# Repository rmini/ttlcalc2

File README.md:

# TtlCalc2 Project

## Overview

The TtlCalc2 project is a recreation of the original (now TtlCalc1) project from 2005 that implemented a four-function floating point calculator in TTL logic without a microprocessor.

This version uses multilayer PCBs and Nixie tube and neon indicators for the display, whereas the original used wire wrap boards and LED 7-segment displays. Both versions share the same architecture, with separate (Harvard architecture) 8-bit data and 12-bit instruction address spaces, a 4-bit data path, and a 16-bit instruction word.

The goal of the original was to gain experience designing and implementing a processor with these techniques with an eye towards taking on the design of a more capable minicomputer. 

This repository contains the hardware and software components for the TtlCalc2 project, including simulation tools, assembly code, and documentation.

## Board renders

### Main logic board (processor)

### Display driver board

### Front panel display board (Nixies and neons)

## Directory Structure

 * [`hw/`](hw/): KiCad schematic and PCB designs for the hardware
 * [`sw/`](sw/): Software for the calculator (microinstruction ROMs)
 * [`doc/`](doc/): Design and implementation documentation
 * [`TtlCalcSim/`](TtlCalcSim/): Simulator for the calculator hardware

## Hardware

The [`hw`](hw) directory contains KiCad project files for the TtlCalc2 hardware design.

- [`ttlcalc2/`](hw/ttlcalc2/): Logic board hardware design files.
- [`ttlcalc2_display/`](hw/ttlcalc2_display/): Display driver module design files.
- [`ttlcalc2_front/`](hw/ttlcalc2_front/): Front panel design files.

TODO: The keyboard and keyboard interface still needs to be designed.

### Gerber Files

The `hw/ttlcalc2/gerbers` directory contains the Gerber files for PCB manufacturing.

## Software

The [`sw`](sw/) directory contains assembly code for the TtlCalc2 project. This project uses the [customasm](https://github.com/hlorenzi/customasm) assembler (v0.14.0 or later) to generate the microcode stream.

- [`ttlcalc2.asm`](sw/ttlcalc2.asm): Mnemonic definitions for the TtlCalc2 microcode.
- [`fib.asm`](sw/fib.asm): Assembly code for calculating Fibonacci numbers.

TODO: Port original ttlcalc assembly source code to new customasm syntax.

### Assembling

For example, to build the Fibonacci code, run:
```sh
customasm fib.asm
```
This generates `fib.bin` which you can then load into the simulator and run.

## Documentation

The [`doc`](doc/) directory contains documentation for the TtlCalc2 project.

## Simulation

The [`TtlCalcSim`](TtlCalcSim/) directory contains the simulation tools for the TtlCalc2 project. The simulator is implemented as a C#/.NET 9.0 console application.

- [`TtlCalcSim/`](TtlCalcSim/TtlCalcSim/): Core simulation library.
- [`TtlCalcSim.ConsoleUI/`](TtlCalcSim/TtlCalcSim.ConsoleUI/): Console-based user interface for the simulator.
- [`TtlCalcSim.Tests/`](TtlCalcSim/TtlCalcSim.Tests/): Unit tests for the simulation library.
- [`TtlCalcSim.Testing/`](TtlCalcSim/TtlCalcSim.Testing/): Helpers for testing assembly programs in the simulator.
- [`TtlCalcSim.ProgramTests/`](TtlCalcSim/TtlCalcSim.ProgramTests/): Tests that assemble programs from [`sw`](sw/) and run them in the simulator, including end-to-end checks of each instruction against the documented behavior.

### Building the Simulator

To build the simulator, open the TtlCalcSim.sln solution file in Visual Studio and build the project, or use the following command from the TtlCalcSim directory:
```sh
dotnet build
```

### Running Tests

To run the unit tests, use the following command from the TtlCalcSim directory:
```sh
dotnet test
```

The program tests assemble source at test time, so they need customasm v0.14.0 or later on `PATH`, or the `CUSTOMASM` environment variable set to its location.

### Testing programs

`TtlCalcSim.Testing` assembles a program with customasm and loads it into a `TestMachine`, which can set up state, run to labels, and inspect results by symbol name:
```csharp
var m = new TestMachine(AsmProgram.AssembleSw("fib.asm"));
m.RunUntil("numloop");                         // program labels; fails if the step limit is hit
Assert.Equal(0x1, m.Mem["src1h"]);             // memory by address or data label
m.RunToEnd(maxSteps: 10_000);
Assert.Equal(832040, m.ReadNumber(0xF8, 8));   // BCD, least significant digit first
```

`StartAt("label")` begins execution elsewhere, so a loop body can be tested in isolation after setting up memory and registers.

`AsmProgram.FromSource` assembles a snippet with the TtlCalc2 rules included, which is useful for testing individual instructions. I/O writes are recorded in `IoWrites`, and input is supplied with `QueueInput` or `OnInput`; reading an address with no input fails the test.

### Running the simulator

Either run the simulator executable after building, or run it via the `dotnet` command:
```sh
dotnet run --project TtlCalcSim.ConsoleUI
```

## License

This project is licensed under the MIT License. See the LICENSE file for details.

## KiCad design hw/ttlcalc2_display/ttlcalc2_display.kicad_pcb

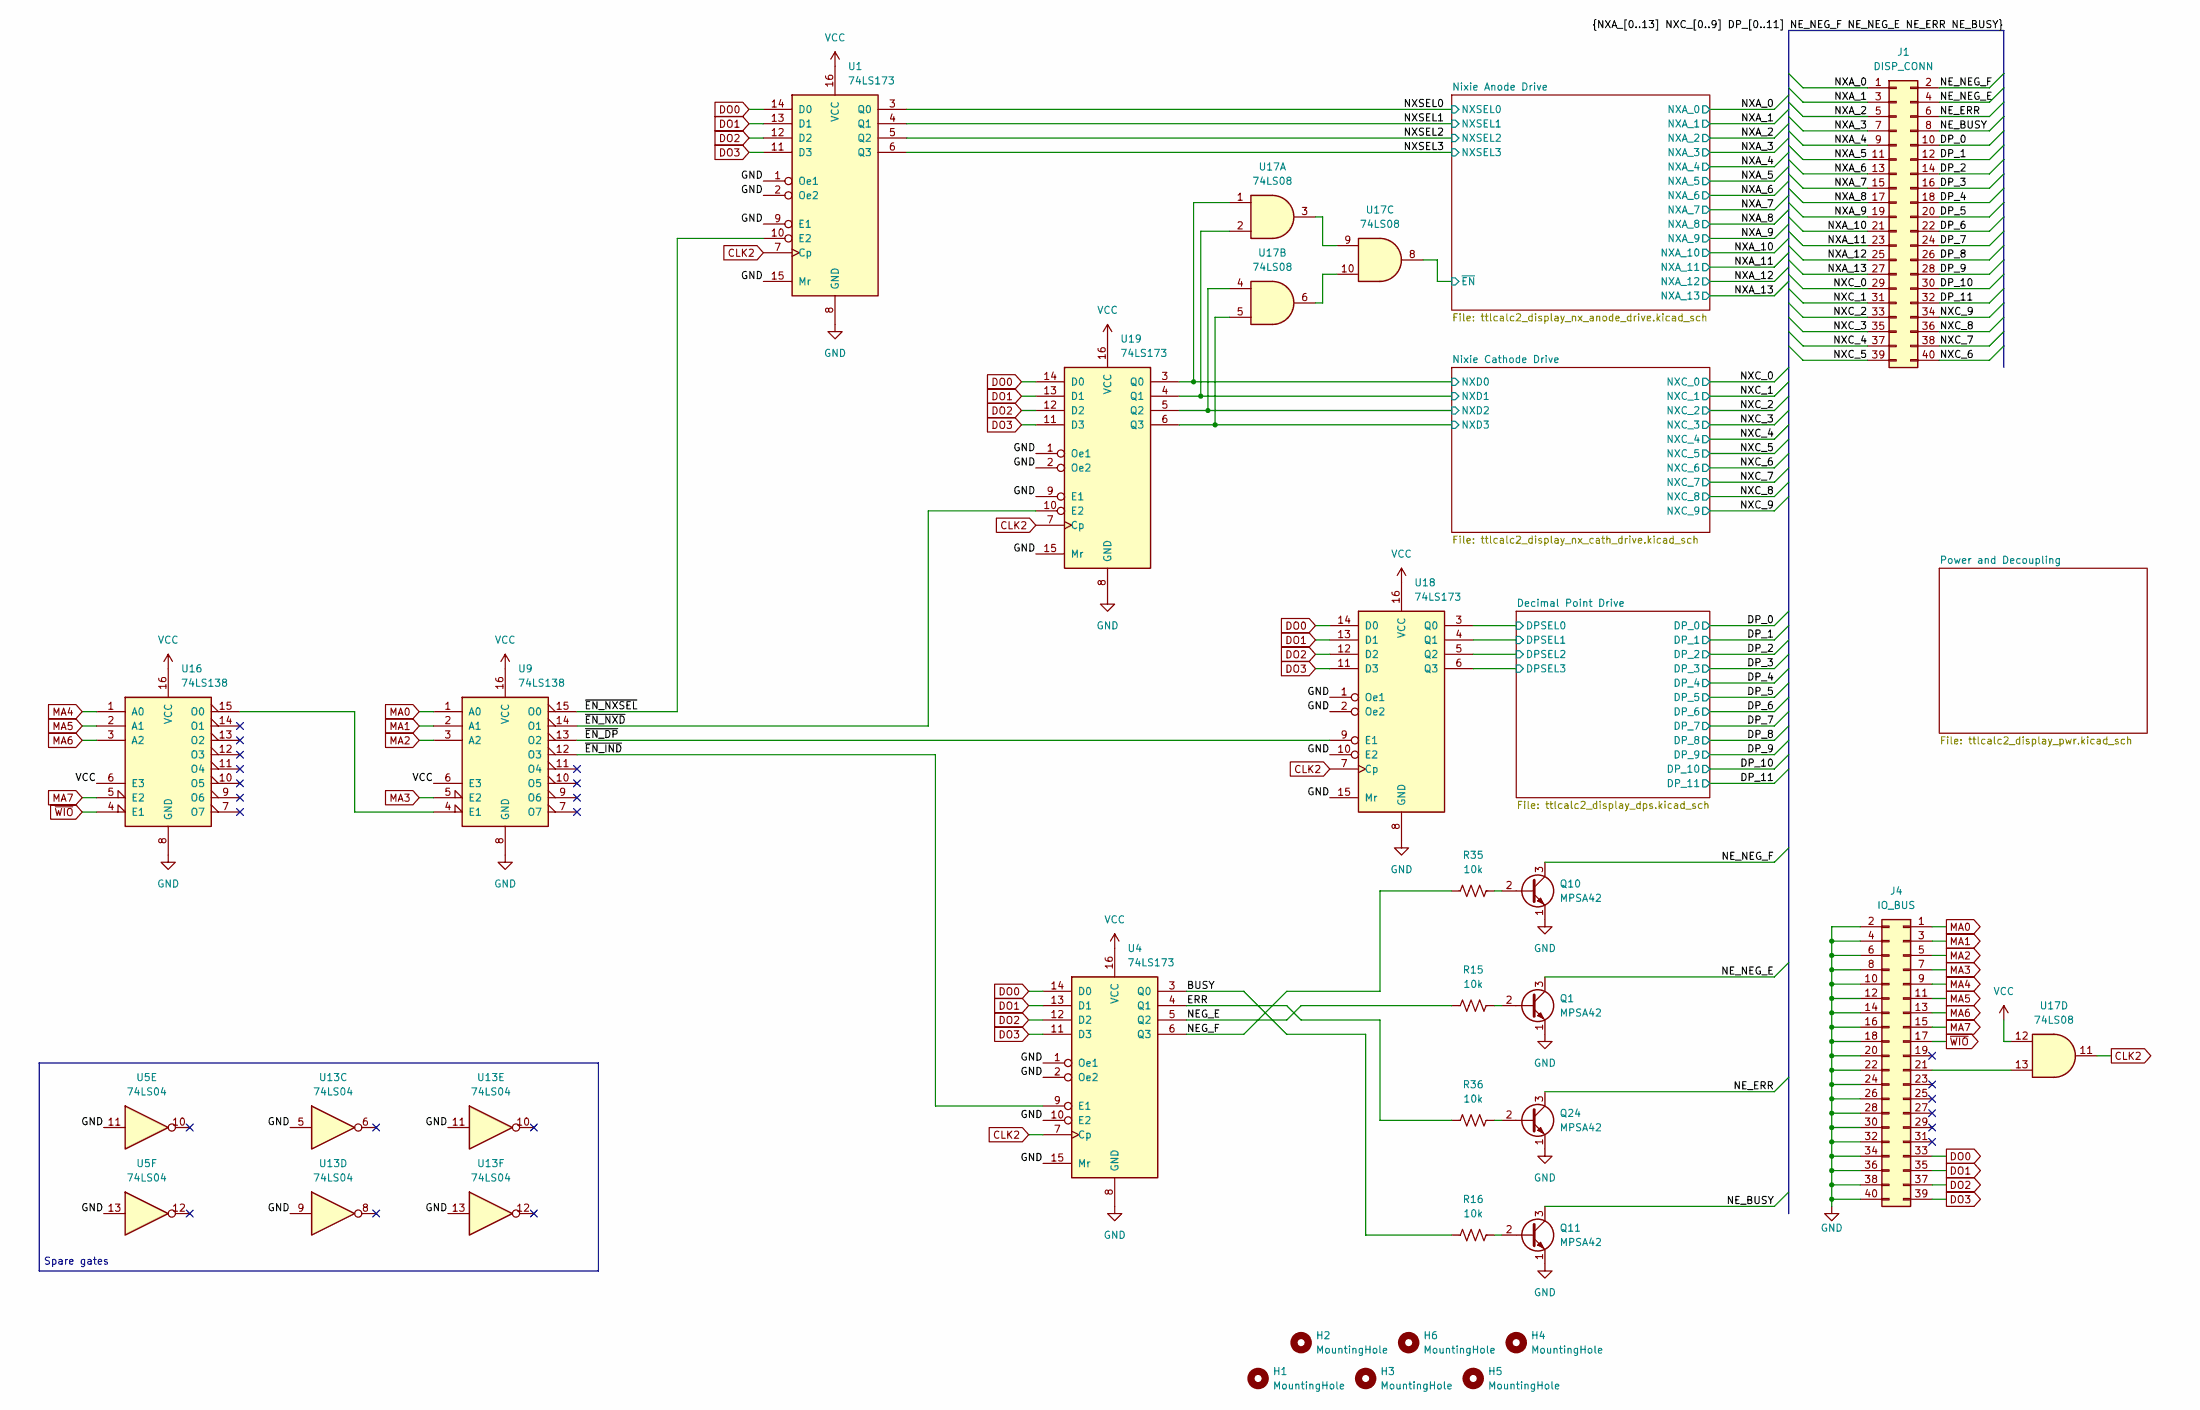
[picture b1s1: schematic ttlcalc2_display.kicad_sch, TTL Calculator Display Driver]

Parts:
H1, H2, H3, H4, H5, H6: MountingHole; MountingHole_3.2mm_M3
J1: DISP_CONN; IDC-Header_2x20_P2.54mm_Vertical
J4: IO_BUS; PinHeader_2x20_P2.54mm_Vertical
Q1, Q10, Q11, Q24: MPSA42; TO-92_Inline_Wide
R15, R16, R35, R36: 10k; R_Axial_DIN0207_L6.3mm_D2.5mm_P7.62mm_Horizontal
U1, U4, U18, U19: 74LS173; DIP-16_W7.62mm
U5, U13: 74LS04; DIP-14_W7.62mm
U9, U16: 74LS138; DIP-16_W7.62mm
U17: 74LS08; DIP-14_W7.62mm

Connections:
/BUSY: R16.1, U4.3 (Q0)
/DP_0: J1.10; also elsewhere on the board
/DP_1: J1.12; also elsewhere on the board
/DP_2: J1.14; also elsewhere on the board
/DP_3: J1.16; also elsewhere on the board
/DP_4: J1.18; also elsewhere on the board
/DP_5: J1.20; also elsewhere on the board
/DP_6: J1.22; also elsewhere on the board
/DP_7: J1.24; also elsewhere on the board
/DP_8: J1.26; also elsewhere on the board
/DP_9: J1.28; also elsewhere on the board
/DP_10: J1.30; also elsewhere on the board
/DP_11: J1.32; also elsewhere on the board
/Decimal Point Drive/DPSEL0: U18.3 (Q0); also elsewhere on the board
/Decimal Point Drive/DPSEL1: U18.4 (Q1); also elsewhere on the board
/Decimal Point Drive/DPSEL2: U18.5 (Q2); also elsewhere on the board
/Decimal Point Drive/DPSEL3: U18.6 (Q3); also elsewhere on the board
/ERR: R36.1, U4.4 (Q1)
/NEG_E: R15.1, U4.5 (Q2)
/NEG_F: R35.1, U4.6 (Q3)
/NE_BUSY: J1.8, Q11.3 (C)
/NE_ERR: J1.6, Q24.3 (C)
/NE_NEG_E: J1.4, Q1.3 (C)
/NE_NEG_F: J1.2, Q10.3 (C)
/NXA_0: J1.1; also elsewhere on the board
/NXA_1: J1.3; also elsewhere on the board
/NXA_2: J1.5; also elsewhere on the board
/NXA_3: J1.7; also elsewhere on the board
/NXA_4: J1.9; also elsewhere on the board
/NXA_5: J1.11; also elsewhere on the board
/NXA_6: J1.13; also elsewhere on the board
/NXA_7: J1.15; also elsewhere on the board
/NXA_8: J1.17; also elsewhere on the board
/NXA_9: J1.19; also elsewhere on the board
/NXA_10: J1.21; also elsewhere on the board
/NXA_11: J1.23; also elsewhere on the board
/NXA_12: J1.25; also elsewhere on the board
/NXA_13: J1.27; also elsewhere on the board
/NXC_0: J1.29; also elsewhere on the board
/NXC_1: J1.31; also elsewhere on the board
/NXC_2: J1.33; also elsewhere on the board
/NXC_3: J1.35; also elsewhere on the board
/NXC_4: J1.37; also elsewhere on the board
/NXC_5: J1.39; also elsewhere on the board
/NXC_6: J1.40; also elsewhere on the board
/NXC_7: J1.38; also elsewhere on the board
/NXC_8: J1.36; also elsewhere on the board
/NXC_9: J1.34; also elsewhere on the board
/NXSEL0: U1.3 (Q0); also elsewhere on the board
/NXSEL1: U1.4 (Q1); also elsewhere on the board
/NXSEL2: U1.5 (Q2); also elsewhere on the board
/NXSEL3: U1.6 (Q3); also elsewhere on the board
/Nixie Anode Drive/~EN: U17.8; also elsewhere on the board
/Nixie Cathode Drive/NXD0: U17.1, U19.3 (Q0); also elsewhere on the board
/Nixie Cathode Drive/NXD1: U17.2, U19.4 (Q1); also elsewhere on the board
/Nixie Cathode Drive/NXD2: U17.4, U19.5 (Q2); also elsewhere on the board
/Nixie Cathode Drive/NXD3: U17.5, U19.6 (Q3); also elsewhere on the board
/~EN_DP: U9.13 (O2), U18.9 (E1)
/~EN_IND: U4.9 (E1), U9.12 (O3)
/~EN_NXD: U9.14 (O1), U19.10 (E2)
/~EN_NXSEL: U1.10 (E2), U9.15 (O0)
CLK2: U1.7 (Cp), U4.7 (Cp), U17.11, U18.7 (Cp), U19.7 (Cp)
DO0: J4.33, U1.14 (D0), U4.14 (D0), U18.14 (D0), U19.14 (D0)
DO1: J4.35, U1.13 (D1), U4.13 (D1), U18.13 (D1), U19.13 (D1)
DO2: J4.37, U1.12 (D2), U4.12 (D2), U18.12 (D2), U19.12 (D2)
DO3: J4.39, U1.11 (D3), U4.11 (D3), U18.11 (D3), U19.11 (D3)
GND: J4.2, J4.4, J4.6, J4.8, J4.10, J4.12, J4.14, J4.16, J4.18, J4.20, J4.22, J4.24, J4.26, J4.28, J4.30, J4.32, J4.34, J4.36, J4.38, J4.40, Q1.1 (E), Q10.1 (E), Q11.1 (E), Q24.1 (E), U1.1 (Oe1), U1.2 (Oe2), U1.8 (GND), U1.9 (E1), U1.15 (Mr), U4.1 (Oe1), U4.2 (Oe2), U4.8 (GND), U4.10 (E2), U4.15 (Mr), U5.11, U5.13, U9.8 (GND), U13.5, U13.9, U13.11, U13.13, U16.8 (GND), U18.1 (Oe1), U18.2 (Oe2), U18.8 (GND), U18.10 (E2), U18.15 (Mr), U19.1 (Oe1), U19.2 (Oe2), U19.8 (GND), U19.9 (E1), U19.15 (Mr); also elsewhere on the board
MA0: J4.1, U9.1 (A0)
MA1: J4.3, U9.2 (A1)
MA2: J4.5, U9.3 (A2)
MA3: J4.7, U9.5 (E2)
MA4: J4.9, U16.1 (A0)
MA5: J4.11, U16.2 (A1)
MA6: J4.13, U16.3 (A2)
MA7: J4.15, U16.5 (E2)
unnamed: J4.21, U17.13
unnamed: Q1.2 (B), R15.2
unnamed: Q10.2 (B), R35.2
unnamed: Q11.2 (B), R16.2
unnamed: Q24.2 (B), R36.2
unnamed: U9.4 (E1), U16.15 (O0)
unnamed: U17.3, U17.9
unnamed: U17.6, U17.10
VCC: U1.16 (VCC), U4.16 (VCC), U9.6 (E3), U9.16 (VCC), U16.6 (E3), U16.16 (VCC), U17.12, U18.16 (VCC), U19.16 (VCC); also elsewhere on the board
~WIO: J4.17, U16.4 (E1)

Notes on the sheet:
Spare gates

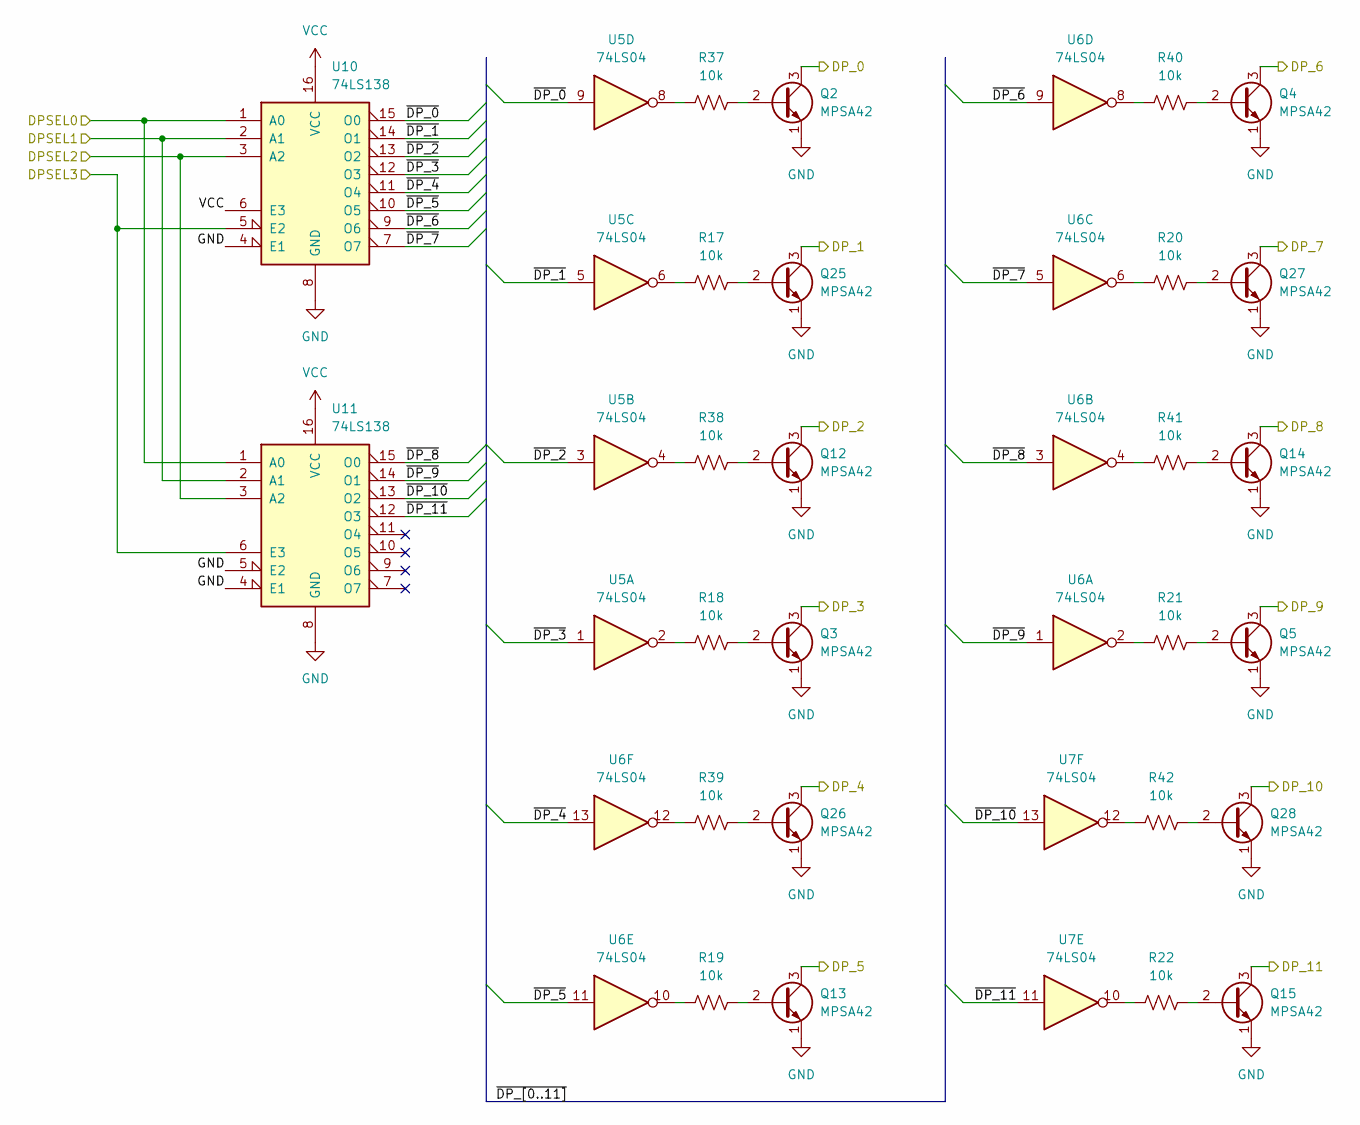
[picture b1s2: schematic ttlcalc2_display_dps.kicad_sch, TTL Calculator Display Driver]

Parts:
Q2, Q3, Q4, Q5, Q12, Q13, Q14, Q15, Q25, Q26, Q27, Q28: MPSA42; TO-92_Inline_Wide
R17, R18, R19, R20, R21, R22, R37, R38, R39, R40, R41, R42: 10k; R_Axial_DIN0207_L6.3mm_D2.5mm_P7.62mm_Horizontal
U5, U6, U7: 74LS04; DIP-14_W7.62mm
U10, U11: 74LS138; DIP-16_W7.62mm

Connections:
/DP_0: Q2.3 (C); also elsewhere on the board
/DP_1: Q25.3 (C); also elsewhere on the board
/DP_2: Q12.3 (C); also elsewhere on the board
/DP_3: Q3.3 (C); also elsewhere on the board
/DP_4: Q26.3 (C); also elsewhere on the board
/DP_5: Q13.3 (C); also elsewhere on the board
/DP_6: Q4.3 (C); also elsewhere on the board
/DP_7: Q27.3 (C); also elsewhere on the board
/DP_8: Q14.3 (C); also elsewhere on the board
/DP_9: Q5.3 (C); also elsewhere on the board
/DP_10: Q28.3 (C); also elsewhere on the board
/DP_11: Q15.3 (C); also elsewhere on the board
/Decimal Point Drive/DPSEL0: U10.1 (A0), U11.1 (A0); also elsewhere on the board
/Decimal Point Drive/DPSEL1: U10.2 (A1), U11.2 (A1); also elsewhere on the board
/Decimal Point Drive/DPSEL2: U10.3 (A2), U11.3 (A2); also elsewhere on the board
/Decimal Point Drive/DPSEL3: U10.5 (E2), U11.6 (E3); also elsewhere on the board
/Decimal Point Drive/~DP_0: U5.9, U10.15 (O0)
/Decimal Point Drive/~DP_1: U5.5, U10.14 (O1)
/Decimal Point Drive/~DP_2: U5.3, U10.13 (O2)
/Decimal Point Drive/~DP_3: U5.1, U10.12 (O3)
/Decimal Point Drive/~DP_4: U6.13, U10.11 (O4)
/Decimal Point Drive/~DP_5: U6.11, U10.10 (O5)
/Decimal Point Drive/~DP_6: U6.9, U10.9 (O6)
/Decimal Point Drive/~DP_7: U6.5, U10.7 (O7)
/Decimal Point Drive/~DP_8: U6.3, U11.15 (O0)
/Decimal Point Drive/~DP_9: U6.1, U11.14 (O1)
/Decimal Point Drive/~DP_10: U7.13, U11.13 (O2)
/Decimal Point Drive/~DP_11: U7.11, U11.12 (O3)
GND: Q2.1 (E), Q3.1 (E), Q4.1 (E), Q5.1 (E), Q12.1 (E), Q13.1 (E), Q14.1 (E), Q15.1 (E), Q25.1 (E), Q26.1 (E), Q27.1 (E), Q28.1 (E), U10.4 (E1), U10.8 (GND), U11.4 (E1), U11.5 (E2), U11.8 (GND); also elsewhere on the board
unnamed: Q2.2 (B), R37.2
unnamed: Q3.2 (B), R18.2
unnamed: Q4.2 (B), R40.2
unnamed: Q5.2 (B), R21.2
unnamed: Q12.2 (B), R38.2
unnamed: Q13.2 (B), R19.2
unnamed: Q14.2 (B), R41.2
unnamed: Q15.2 (B), R22.2
unnamed: Q25.2 (B), R17.2
unnamed: Q26.2 (B), R39.2
unnamed: Q27.2 (B), R20.2
unnamed: Q28.2 (B), R42.2
unnamed: R17.1, U5.6
unnamed: R18.1, U5.2
unnamed: R19.1, U6.10
unnamed: R20.1, U6.6
unnamed: R21.1, U6.2
unnamed: R22.1, U7.10
unnamed: R37.1, U5.8
unnamed: R38.1, U5.4
unnamed: R39.1, U6.12
unnamed: R40.1, U6.8
unnamed: R41.1, U6.4
unnamed: R42.1, U7.12
VCC: U10.6 (E3), U10.16 (VCC), U11.16 (VCC); also elsewhere on the board

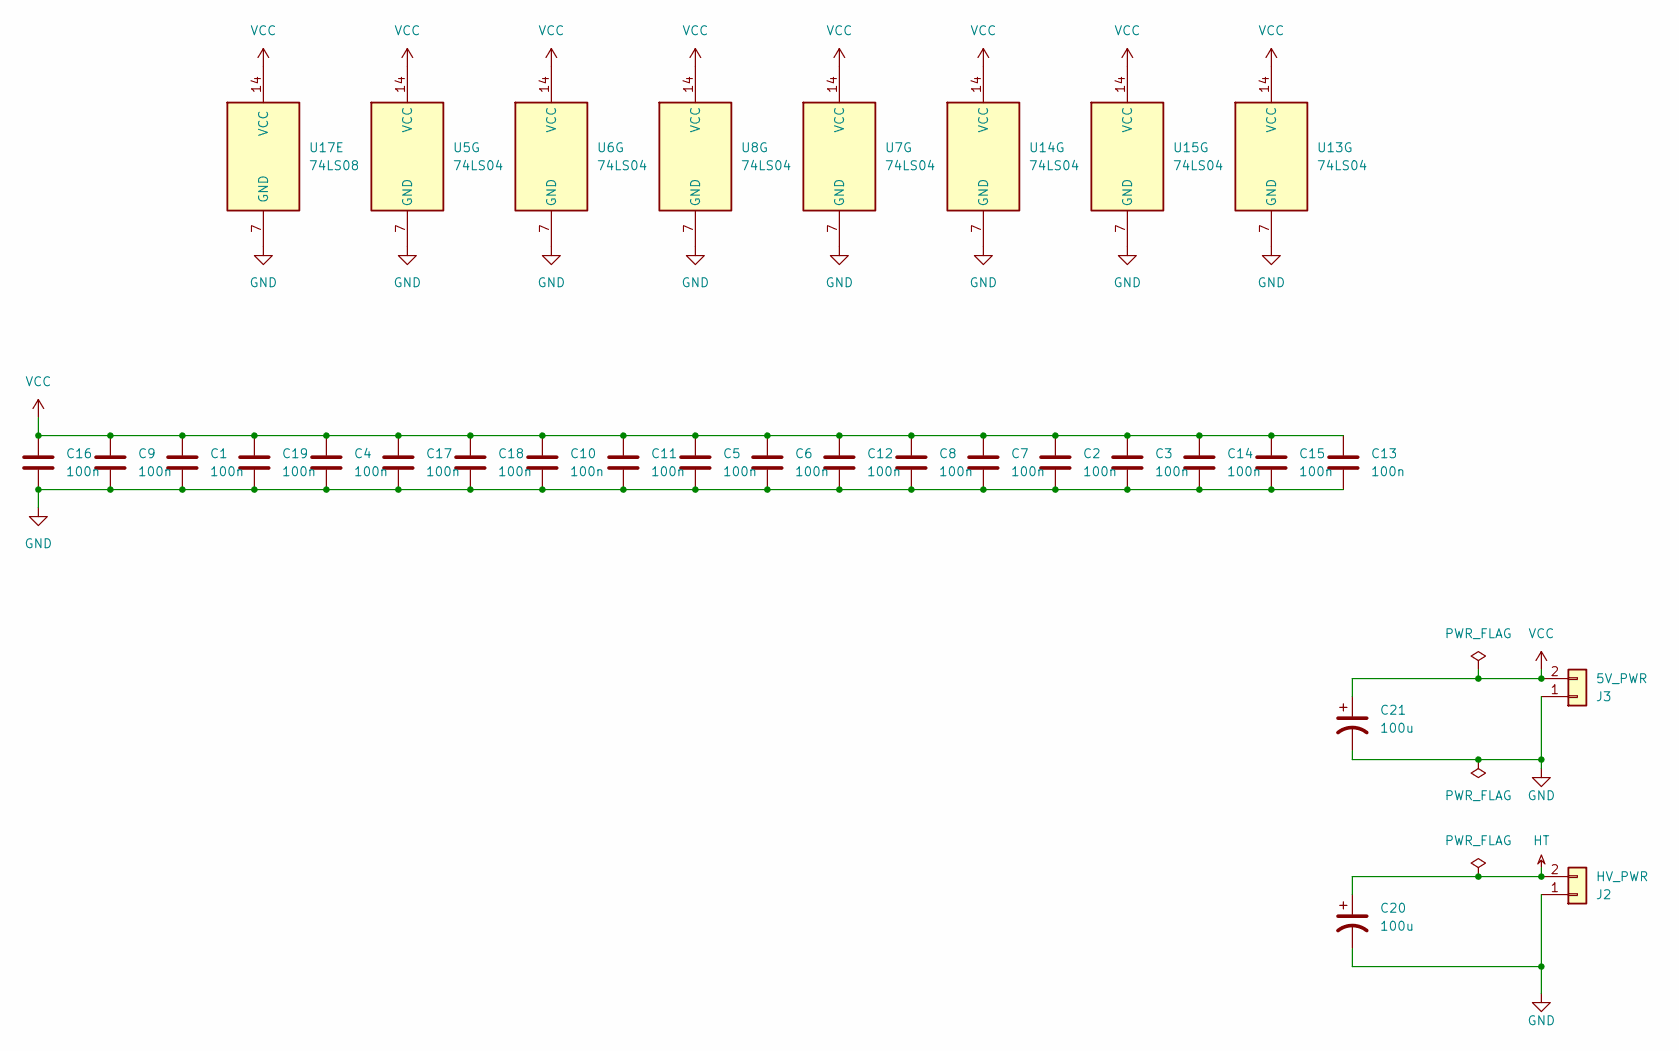
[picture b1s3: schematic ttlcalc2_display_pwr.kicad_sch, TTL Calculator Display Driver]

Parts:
C1, C2, C3, C4, C5, C6, C7, C8, C9, C10, C11, C12, C13, C14, C15, C16, C17, C18, C19: 100n; C_Axial_L3.8mm_D2.6mm_P7.50mm_Horizontal
C20: 100u; CP_Radial_D18.0mm_P7.50mm
C21: 100u; CP_Radial_D6.3mm_P2.50mm
J2: HV_PWR; TerminalBlock_Phoenix_MKDS-1,5-2-5.08_1x02_P5.08mm_Horizont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
J3: 5V_PWR; TerminalBlock_Phoenix_MKDS-1,5-2-5.08_1x02_P5.08mm_Horizont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
U5, U6, U7, U8, U13, U14, U15: 74LS04; DIP-14_W7.62mm
U17: 74LS08; DIP-14_W7.62mm

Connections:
GND: C1.2, C2.2, C3.2, C4.2, C5.2, C6.2, C7.2, C8.2, C9.2, C10.2, C11.2, C12.2, C13.2, C14.2, C15.2, C16.2, C17.2, C18.2, C19.2, C20.2, C21.2, J2.1, J3.1, U5.7 (GND), U6.7 (GND), U7.7 (GND), U8.7 (GND), U13.7 (GND), U14.7 (GND), U15.7 (GND), U17.7 (GND); also elsewhere on the board
HT: C20.1, J2.2; also elsewhere on the board
VCC: C1.1, C2.1, C3.1, C4.1, C5.1, C6.1, C7.1, C8.1, C9.1, C10.1, C11.1, C12.1, C13.1, C14.1, C15.1, C16.1, C17.1, C18.1, C19.1, C21.1, J3.2, U5.14 (VCC), U6.14 (VCC), U7.14 (VCC), U8.14 (VCC), U13.14 (VCC), U14.14 (VCC), U15.14 (VCC), U17.14 (VCC); also elsewhere on the board

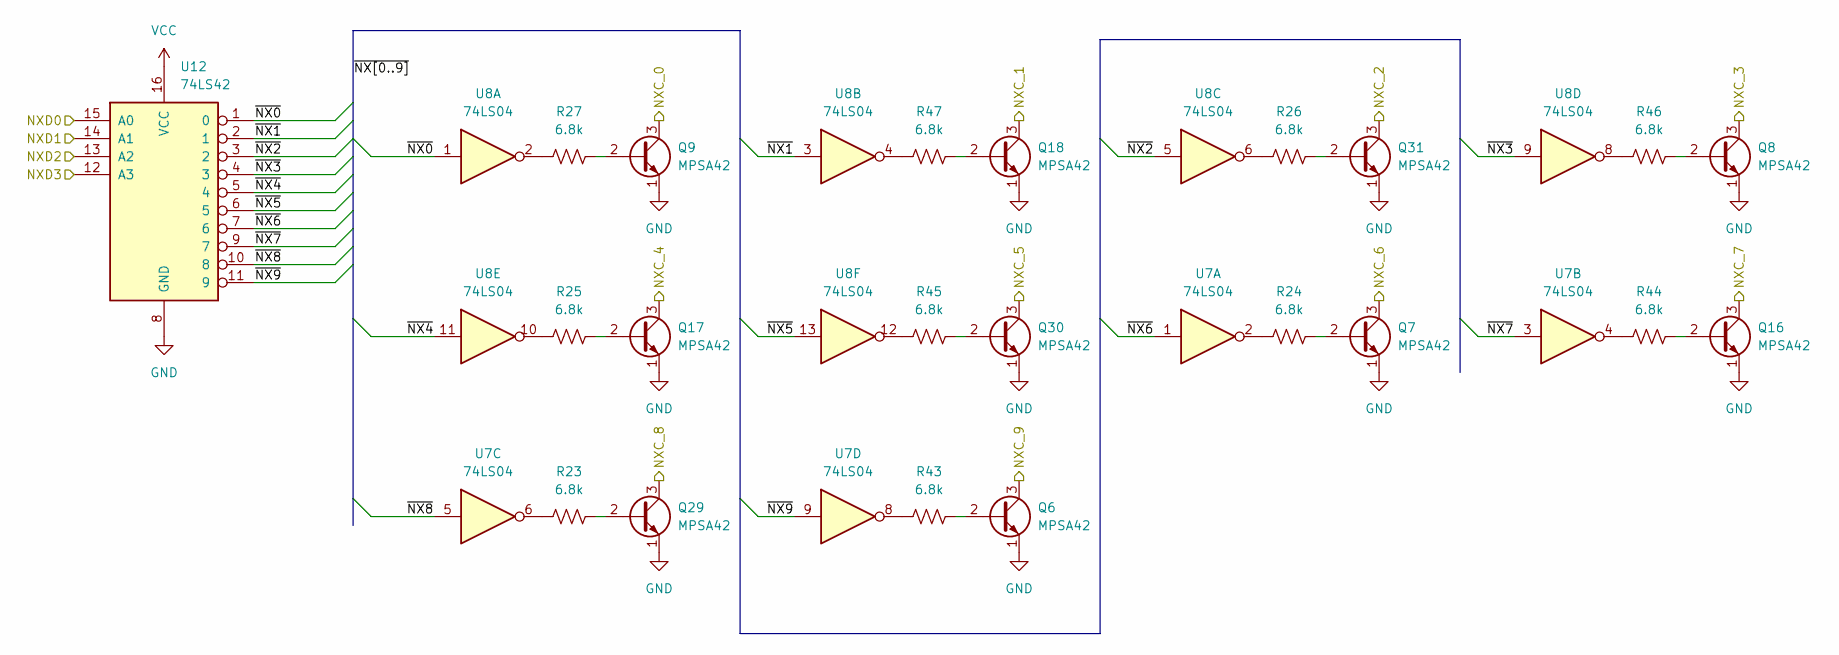
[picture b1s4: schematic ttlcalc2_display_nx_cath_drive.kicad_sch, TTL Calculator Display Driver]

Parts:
Q6, Q7, Q8, Q9, Q16, Q17, Q18, Q29, Q30, Q31: MPSA42; TO-92_Inline_Wide
R23, R24, R25, R26, R27, R43, R44, R45, R46, R47: 6.8k; R_Axial_DIN0207_L6.3mm_D2.5mm_P7.62mm_Horizontal
U7, U8: 74LS04; DIP-14_W7.62mm
U12: 74LS42; DIP-16_W7.62mm

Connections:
/NXC_0: Q9.3 (C); also elsewhere on the board
/NXC_1: Q18.3 (C); also elsewhere on the board
/NXC_2: Q31.3 (C); also elsewhere on the board
/NXC_3: Q8.3 (C); also elsewhere on the board
/NXC_4: Q17.3 (C); also elsewhere on the board
/NXC_5: Q30.3 (C); also elsewhere on the board
/NXC_6: Q7.3 (C); also elsewhere on the board
/NXC_7: Q16.3 (C); also elsewhere on the board
/NXC_8: Q29.3 (C); also elsewhere on the board
/NXC_9: Q6.3 (C); also elsewhere on the board
/Nixie Cathode Drive/NXD0: U12.15 (A0); also elsewhere on the board
/Nixie Cathode Drive/NXD1: U12.14 (A1); also elsewhere on the board
/Nixie Cathode Drive/NXD2: U12.13 (A2); also elsewhere on the board
/Nixie Cathode Drive/NXD3: U12.12 (A3); also elsewhere on the board
/Nixie Cathode Drive/~NX0: U8.1, U12.1 (0)
/Nixie Cathode Drive/~NX1: U8.3, U12.2 (1)
/Nixie Cathode Drive/~NX2: U8.5, U12.3 (2)
/Nixie Cathode Drive/~NX3: U8.9, U12.4 (3)
/Nixie Cathode Drive/~NX4: U8.11, U12.5 (4)
/Nixie Cathode Drive/~NX5: U8.13, U12.6 (5)
/Nixie Cathode Drive/~NX6: U7.1, U12.7 (6)
/Nixie Cathode Drive/~NX7: U7.3, U12.9 (7)
/Nixie Cathode Drive/~NX8: U7.5, U12.10 (8)
/Nixie Cathode Drive/~NX9: U7.9, U12.11 (9)
GND: Q6.1 (E), Q7.1 (E), Q8.1 (E), Q9.1 (E), Q16.1 (E), Q17.1 (E), Q18.1 (E), Q29.1 (E), Q30.1 (E), Q31.1 (E), U12.8 (GND); also elsewhere on the board
unnamed: Q6.2 (B), R43.2
unnamed: Q7.2 (B), R24.2
unnamed: Q8.2 (B), R46.2
unnamed: Q9.2 (B), R27.2
unnamed: Q16.2 (B), R44.2
unnamed: Q17.2 (B), R25.2
unnamed: Q18.2 (B), R47.2
unnamed: Q29.2 (B), R23.2
unnamed: Q30.2 (B), R45.2
unnamed: Q31.2 (B), R26.2
unnamed: R23.1, U7.6
unnamed: R24.1, U7.2
unnamed: R25.1, U8.10
unnamed: R26.1, U8.6
unnamed: R27.1, U8.2
unnamed: R43.1, U7.8
unnamed: R44.1, U7.4
unnamed: R45.1, U8.12
unnamed: R46.1, U8.8
unnamed: R47.1, U8.4
VCC: U12.16 (VCC); also elsewhere on the board

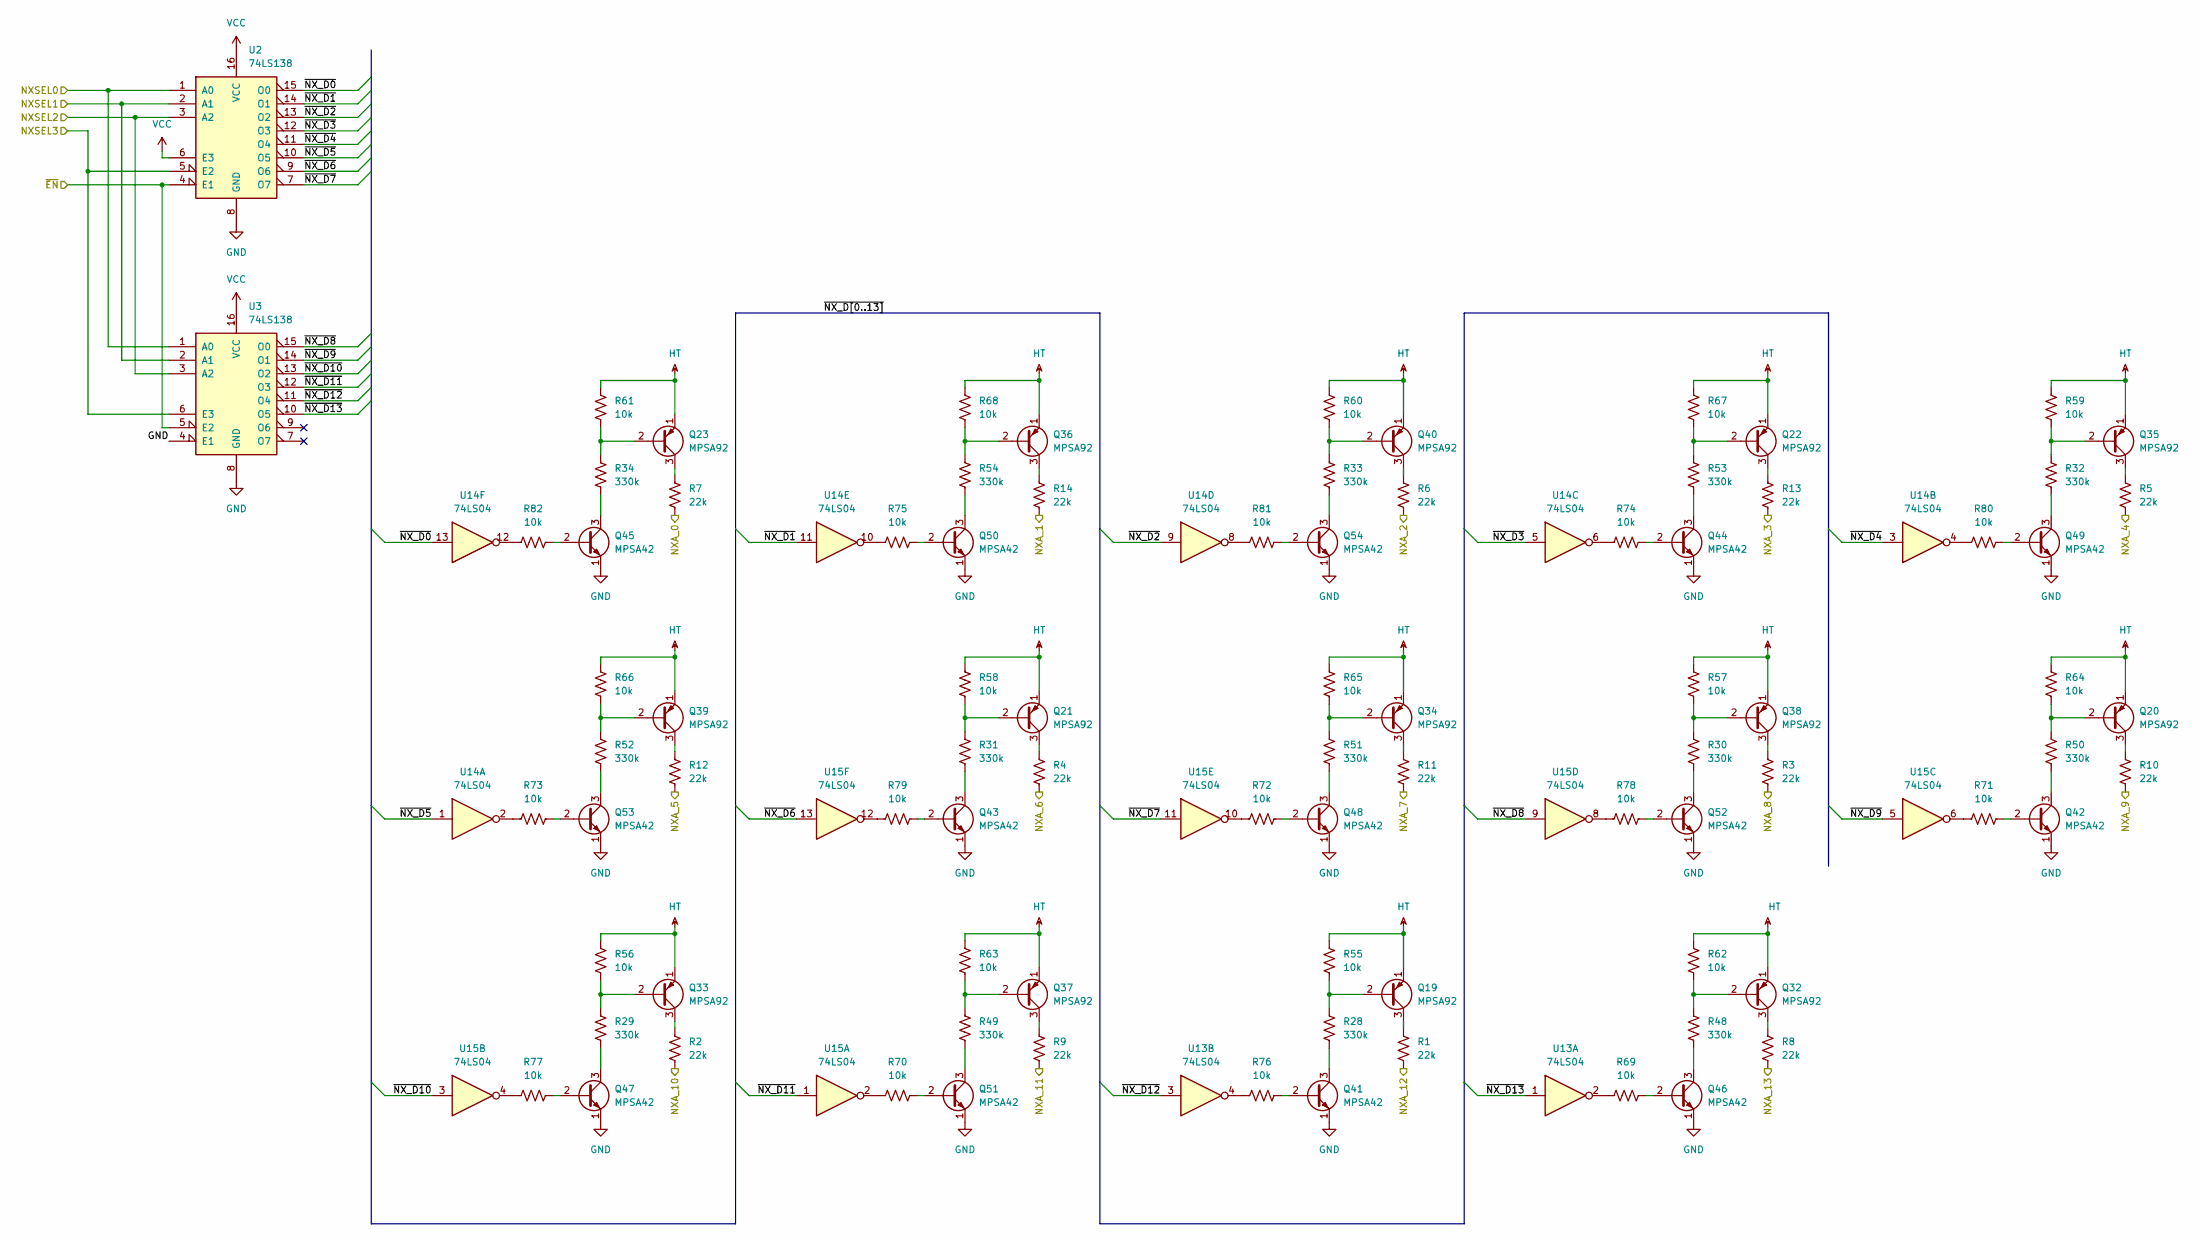
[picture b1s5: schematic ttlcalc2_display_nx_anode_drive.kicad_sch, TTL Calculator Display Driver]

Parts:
Q19, Q20, Q21, Q22, Q23, Q32, Q33, Q34, Q35, Q36, Q37, Q38, Q39, Q40: MPSA92; TO-92_Inline_Wide
Q41, Q42, Q43, Q44, Q45, Q46, Q47, Q48, Q49, Q50, Q51, Q52, Q53, Q54: MPSA42; TO-92_Inline_Wide
R1, R2, R3, R4, R5, R6, R7, R8, R9, R10, R11, R12, R13, R14: 22k; R_Axial_DIN0207_L6.3mm_D2.5mm_P7.62mm_Horizontal
R28, R29, R30, R31, R32, R33, R34, R48, R49, R50, R51, R52, R53, R54: 330k; R_Axial_DIN0207_L6.3mm_D2.5mm_P7.62mm_Horizontal
R55, R56, R57, R58, R59, R60, R61, R62, R63, R64, R65, R66, R67, R68, R69, R70, R71, R72, R73, R74, R75, R76, R77, R78, R79, R80, R81, R82: 10k; R_Axial_DIN0207_L6.3mm_D2.5mm_P7.62mm_Horizontal
U2, U3: 74LS138; DIP-16_W7.62mm
U13, U14, U15: 74LS04; DIP-14_W7.62mm

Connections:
/NXA_0: R7.2; also elsewhere on the board
/NXA_1: R14.2; also elsewhere on the board
/NXA_2: R6.2; also elsewhere on the board
/NXA_3: R13.2; also elsewhere on the board
/NXA_4: R5.2; also elsewhere on the board
/NXA_5: R12.2; also elsewhere on the board
/NXA_6: R4.2; also elsewhere on the board
/NXA_7: R11.2; also elsewhere on the board
/NXA_8: R3.2; also elsewhere on the board
/NXA_9: R10.2; also elsewhere on the board
/NXA_10: R2.2; also elsewhere on the board
/NXA_11: R9.2; also elsewhere on the board
/NXA_12: R1.2; also elsewhere on the board
/NXA_13: R8.2; also elsewhere on the board
/NXSEL0: U2.1 (A0), U3.1 (A0); also elsewhere on the board
/NXSEL1: U2.2 (A1), U3.2 (A1); also elsewhere on the board
/NXSEL2: U2.3 (A2), U3.3 (A2); also elsewhere on the board
/NXSEL3: U2.5 (E2), U3.6 (E3); also elsewhere on the board
/Nixie Anode Drive/~EN: U2.4 (E1), U3.5 (E2); also elsewhere on the board
/Nixie Anode Drive/~NX_D0: U2.15 (O0), U14.13
/Nixie Anode Drive/~NX_D1: U2.14 (O1), U14.11
/Nixie Anode Drive/~NX_D2: U2.13 (O2), U14.9
/Nixie Anode Drive/~NX_D3: U2.12 (O3), U14.5
/Nixie Anode Drive/~NX_D4: U2.11 (O4), U14.3
/Nixie Anode Drive/~NX_D5: U2.10 (O5), U14.1
/Nixie Anode Drive/~NX_D6: U2.9 (O6), U15.13
/Nixie Anode Drive/~NX_D7: U2.7 (O7), U15.11
/Nixie Anode Drive/~NX_D8: U3.15 (O0), U15.9
/Nixie Anode Drive/~NX_D9: U3.14 (O1), U15.5
/Nixie Anode Drive/~NX_D10: U3.13 (O2), U15.3
/Nixie Anode Drive/~NX_D11: U3.12 (O3), U15.1
/Nixie Anode Drive/~NX_D12: U3.11 (O4), U13.3
/Nixie Anode Drive/~NX_D13: U3.10 (O5), U13.1
GND: Q41.1 (E), Q42.1 (E), Q43.1 (E), Q44.1 (E), Q45.1 (E), Q46.1 (E), Q47.1 (E), Q48.1 (E), Q49.1 (E), Q50.1 (E), Q51.1 (E), Q52.1 (E), Q53.1 (E), Q54.1 (E), U2.8 (GND), U3.4 (E1), U3.8 (GND); also elsewhere on the board
HT: Q19.1 (E), Q20.1 (E), Q21.1 (E), Q22.1 (E), Q23.1 (E), Q32.1 (E), Q33.1 (E), Q34.1 (E), Q35.1 (E), Q36.1 (E), Q37.1 (E), Q38.1 (E), Q39.1 (E), Q40.1 (E), R55.1, R56.1, R57.1, R58.1, R59.1, R60.1, R61.1, R62.1, R63.1, R64.1, R65.1, R66.1, R67.1, R68.1; also elsewhere on the board
unnamed: Q19.2 (B), R28.1, R55.2
unnamed: Q19.3 (C), R1.1
unnamed: Q20.2 (B), R50.1, R64.2
unnamed: Q20.3 (C), R10.1
unnamed: Q21.2 (B), R31.1, R58.2
unnamed: Q21.3 (C), R4.1
unnamed: Q22.2 (B), R53.1, R67.2
unnamed: Q22.3 (C), R13.1
unnamed: Q23.2 (B), R34.1, R61.2
unnamed: Q23.3 (C), R7.1
unnamed: Q32.2 (B), R48.1, R62.2
unnamed: Q32.3 (C), R8.1
unnamed: Q33.2 (B), R29.1, R56.2
unnamed: Q33.3 (C), R2.1
unnamed: Q34.2 (B), R51.1, R65.2
unnamed: Q34.3 (C), R11.1
unnamed: Q35.2 (B), R32.1, R59.2
unnamed: Q35.3 (C), R5.1
unnamed: Q36.2 (B), R54.1, R68.2
unnamed: Q36.3 (C), R14.1
unnamed: Q37.2 (B), R49.1, R63.2
unnamed: Q37.3 (C), R9.1
unnamed: Q38.2 (B), R30.1, R57.2
unnamed: Q38.3 (C), R3.1
unnamed: Q39.2 (B), R52.1, R66.2
unnamed: Q39.3 (C), R12.1
unnamed: Q40.2 (B), R33.1, R60.2
unnamed: Q40.3 (C), R6.1
unnamed: Q41.2 (B), R76.2
unnamed: Q41.3 (C), R28.2
unnamed: Q42.2 (B), R71.2
unnamed: Q42.3 (C), R50.2
unnamed: Q43.2 (B), R79.2
unnamed: Q43.3 (C), R31.2
unnamed: Q44.2 (B), R74.2
unnamed: Q44.3 (C), R53.2
unnamed: Q45.2 (B), R82.2
unnamed: Q45.3 (C), R34.2
unnamed: Q46.2 (B), R69.2
unnamed: Q46.3 (C), R48.2
unnamed: Q47.2 (B), R77.2
unnamed: Q47.3 (C), R29.2
unnamed: Q48.2 (B), R72.2
unnamed: Q48.3 (C), R51.2
unnamed: Q49.2 (B), R80.2
unnamed: Q49.3 (C), R32.2
unnamed: Q50.2 (B), R75.2
unnamed: Q50.3 (C), R54.2
unnamed: Q51.2 (B), R70.2
unnamed: Q51.3 (C), R49.2
unnamed: Q52.2 (B), R78.2
unnamed: Q52.3 (C), R30.2
unnamed: Q53.2 (B), R73.2
unnamed: Q53.3 (C), R52.2
unnamed: Q54.2 (B), R81.2
unnamed: Q54.3 (C), R33.2
unnamed: R69.1, U13.2
unnamed: R70.1, U15.2
unnamed: R71.1, U15.6
unnamed: R72.1, U15.10
unnamed: R73.1, U14.2
unnamed: R74.1, U14.6
unnamed: R75.1, U14.10
unnamed: R76.1, U13.4
unnamed: R77.1, U15.4
unnamed: R78.1, U15.8
unnamed: R79.1, U15.12
unnamed: R80.1, U14.4
unnamed: R81.1, U14.8
unnamed: R82.1, U14.12
VCC: U2.6 (E3), U2.16 (VCC), U3.16 (VCC); also elsewhere on the board

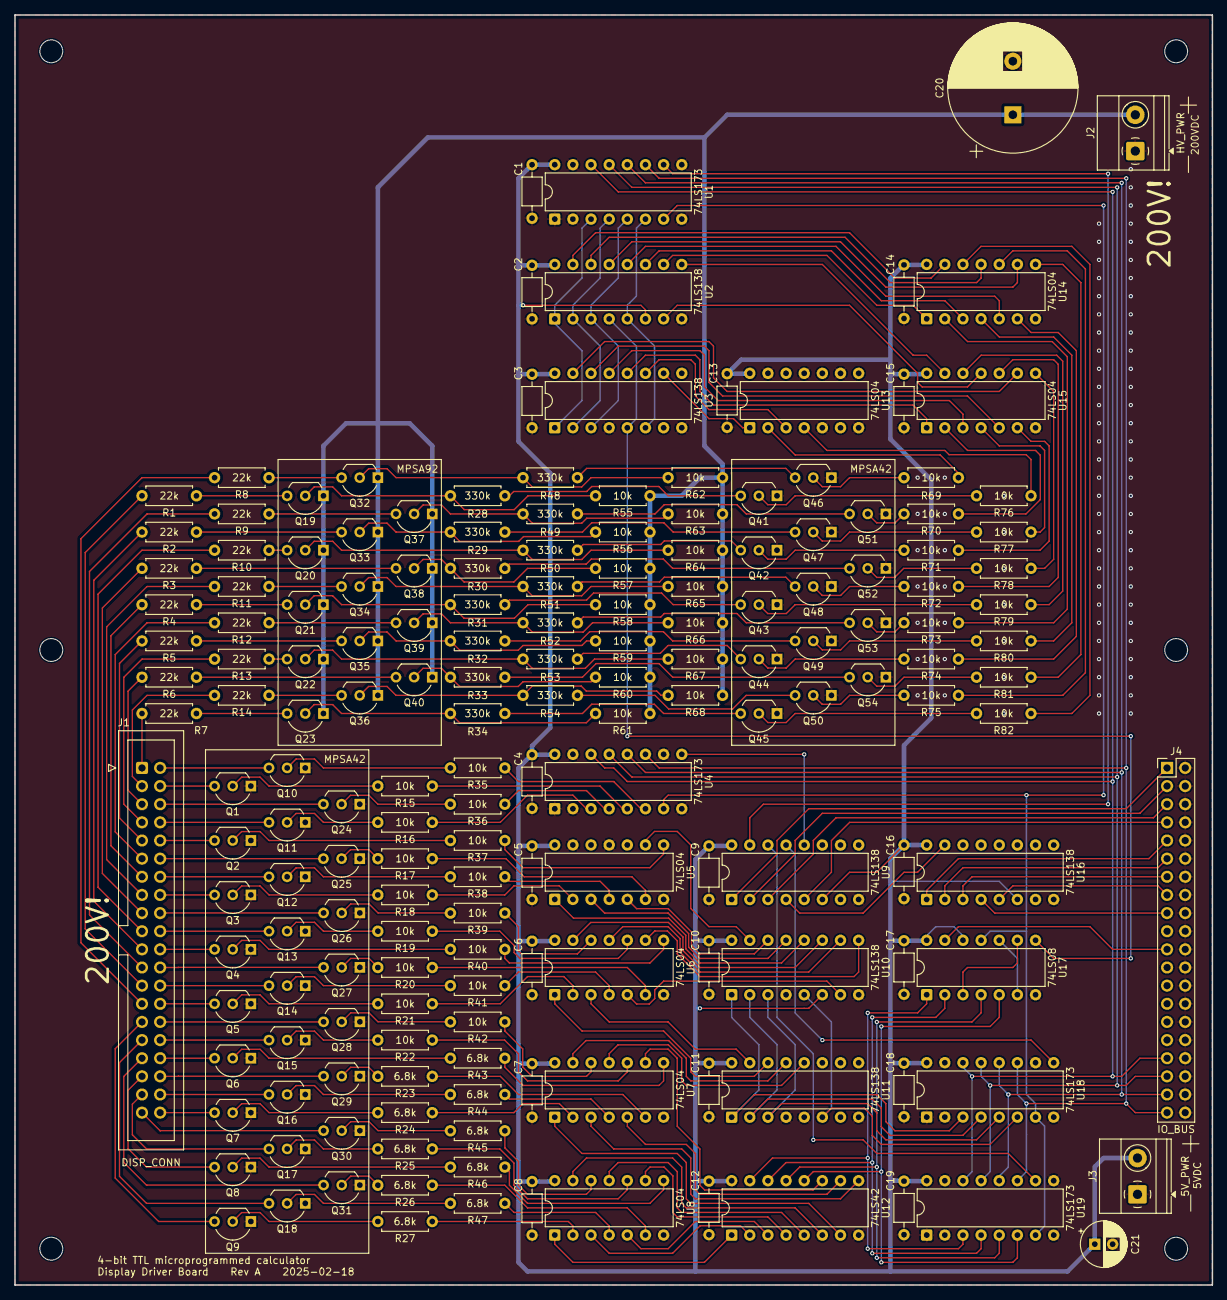
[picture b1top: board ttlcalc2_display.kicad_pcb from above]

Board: 2 copper layers, 167.6 x 177.8 mm, 186 parts (0 on the bottom side), 236 nets.
